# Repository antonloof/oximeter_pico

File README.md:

# Oximeter for the Raspberry pi PICO

ETA-dagen projekt 2022. Mäter din puls och visar den på ett par 7segmentsdisplayer

## 7 Segment
Använder [PIO](https://www.raspberrypi.com/news/what-is-pio/) för att [multiplexa](https://embedded-lab.com/blog/lab-11-multiplexing-seven-segment-led-displays/) displayerna.
PIO matas kontinuerligt av DMA med minimal interaktion från processorn. 

## Hur mäter man puls
Kort svar. Du mäter hur blodet rör sig i dina ådror. Syrerikt och syrfattigt blod absorberar och reflekterar olika mycket ljus.
Vi mäter hur mycket ljus som absorberar av bloded och får reda på om det finns mycket eller lite syre i blodet. 
Ett hjärtslag består av att först trycka ut syrerikt blod och sedan suga tillbaka syrefattigt blod. Det innenbär att ett slag innebär en ökning och sedan en miskning av mängden syre i blodet. Koden filtrerar först "hur mycket syre finns det i blodet"-signalen för att minska bruset. Efter det mäter den tiden mellan maximum av signalen. Detta är periodtiden på dina hjärtslag 1/period ger frekvens.

## Filter?
Vi använder ett 2a ordningens digitalt butterwurth filter. Ni kommer lära er mer om dessa snart (tm) i tex Kretsanalys. 

## Hur hittar vi maximum?
Vi letar efter toppar i signalen som omringas av en dal före och en dal efter. Dessa dalar måste vara "djupa" i förhållande till signalen för att vi ska räkna toppen som en topp. 

## Hur kommer man igång?
https://github.com/ndabas/pico-setup-windows
Ladda ner och kör, detta installerar vscode och toolchain för att bygga projektet och programmera din PICO.

## Vilken sektion?
E!

## Vilken färg?
GUL!

## Vilket skyddshelgon?
KALLE ANKA!

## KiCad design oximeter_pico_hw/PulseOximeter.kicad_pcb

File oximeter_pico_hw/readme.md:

# HW sidan av projektet

## Förklaring av schema

- U1 är våran mikrokontrollermodul, som sköter allting.
- U2 är själva sensor som mäter puls och blodsyrenivåer genom att lysa lite LEDs, som styrs med transistorer Q5-Q7, och mäta hur stark är ljuset efter den går igenom cellerna i din finger. Den innehåller en fotodiod, som släpper en viss mängd ström beroende på ljusstyrkan- tillsammans med R9 bildar den en sorts variabel spänningsdelare, och resulterande analogt värde läses av Pico:n.
- U3 och U4 är 7-segmentsdisplayer, och båda innehåller LED:s för 2 siffror. Segmenter tänds genom själva pinnarna av Pico:n, och transistorer Q1-Q4 väljer vilken segment ska lysa. Resistorer R1-R8 begränsar ström som segmenter ska ta.

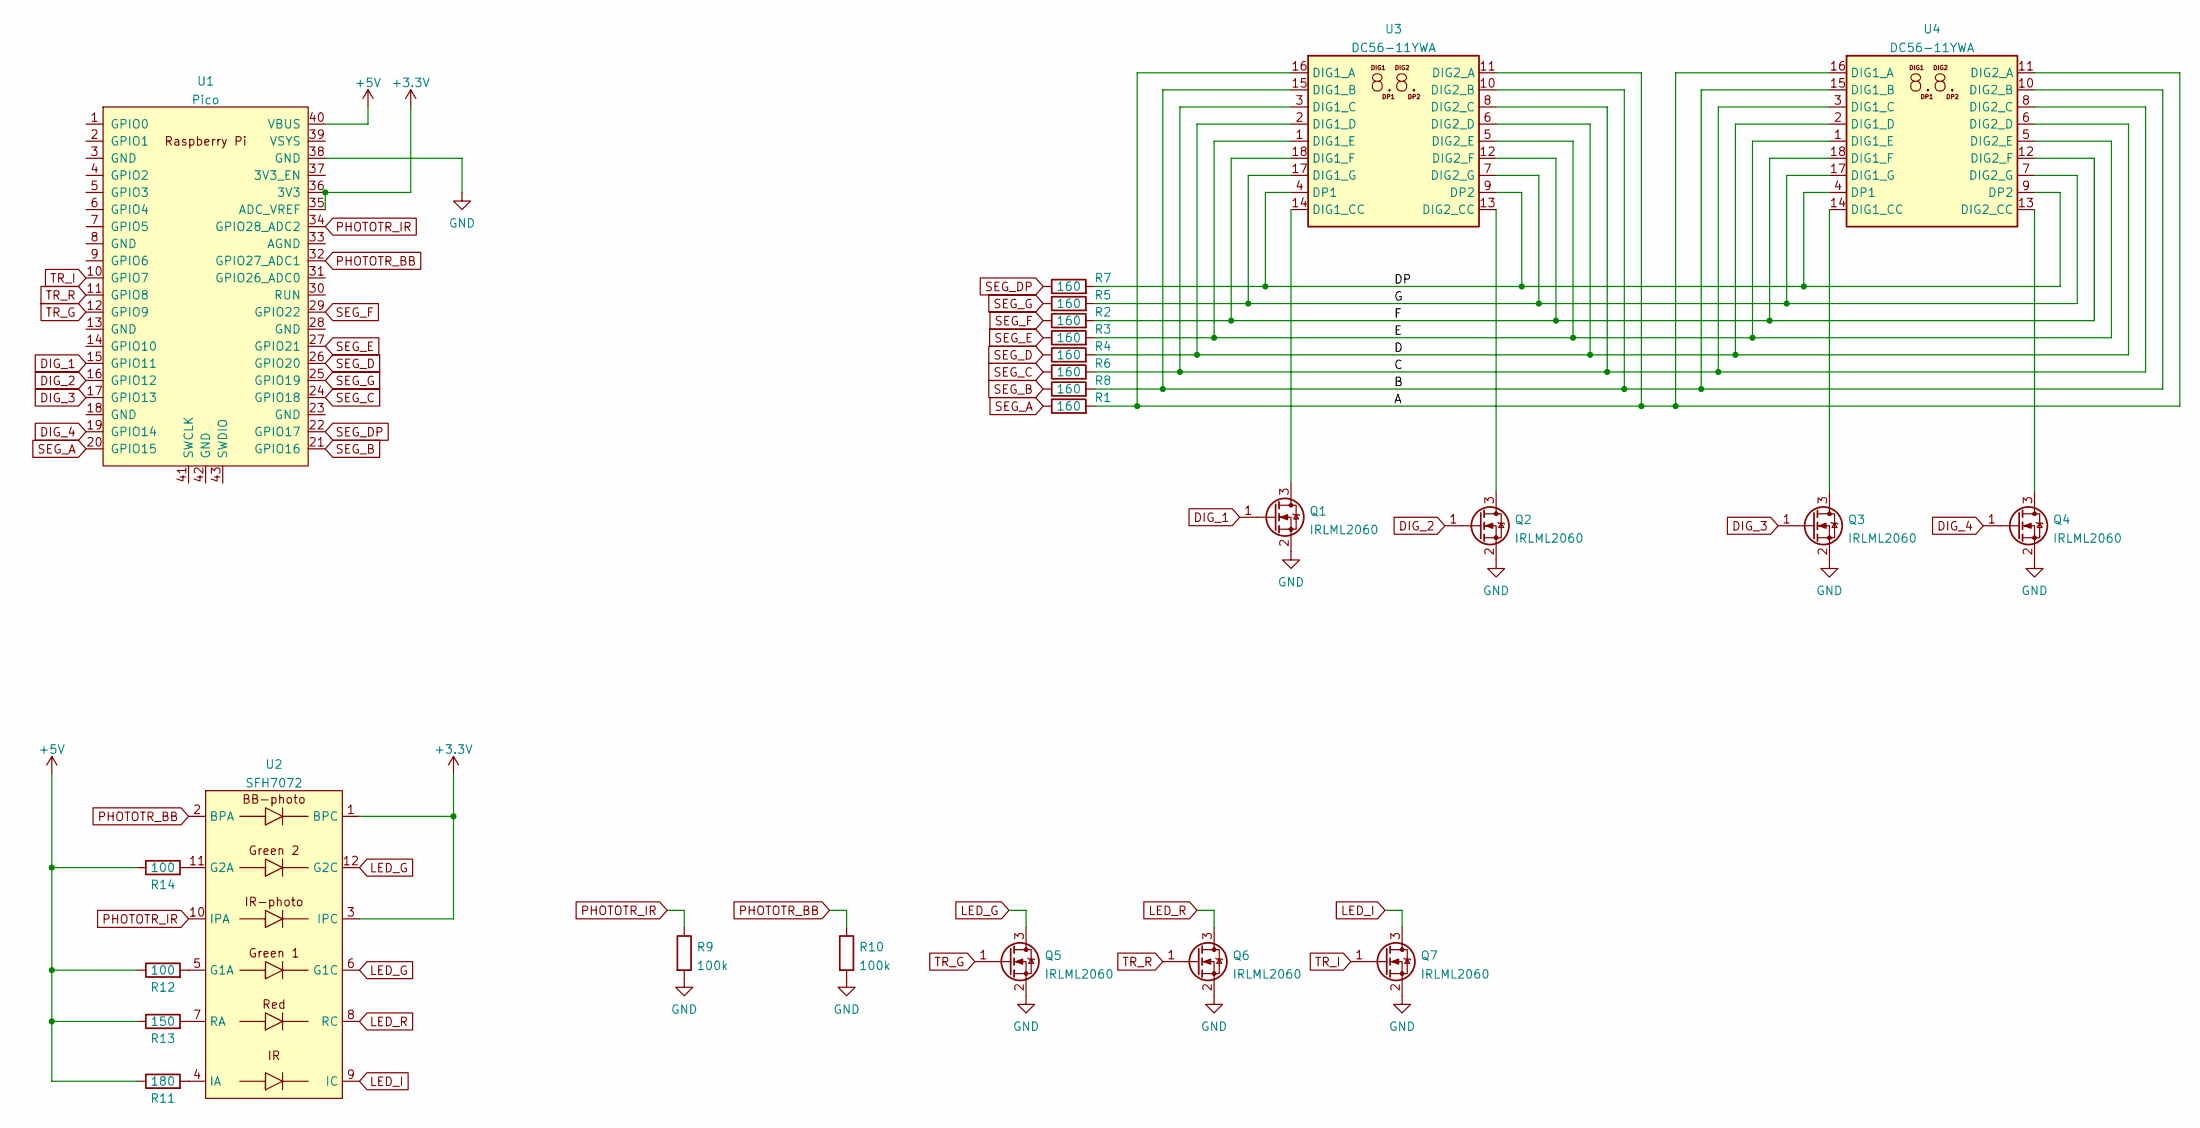
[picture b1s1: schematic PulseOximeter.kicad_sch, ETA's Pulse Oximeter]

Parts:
Q1, Q2, Q3, Q4, Q5, Q6, Q7: IRLML2060; SOT-23
R1, R2, R3, R4, R5, R6, R7, R8: 160; R_Axial_DIN0207_L6.3mm_D2.5mm_P15.24mm_Horizontal
R9, R10: 100k; R_Axial_DIN0207_L6.3mm_D2.5mm_P15.24mm_Horizontal
R11: 180; R_Axial_DIN0207_L6.3mm_D2.5mm_P15.24mm_Horizontal
R12, R14: 100; R_Axial_DIN0207_L6.3mm_D2.5mm_P15.24mm_Horizontal
R13: 150; R_Axial_DIN0207_L6.3mm_D2.5mm_P15.24mm_Horizontal
U1: Pico; RPi_Pico_SMD_TH
U2: SFH7072
U3, U4: DC56-11YWA; DA56-11SYKWA

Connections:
+3V3: U1.35 (ADC_VREF), U1.36 (3V3), U2.1 (BPC), U2.3 (IPC)
+5V: R11.1, R12.1, R13.1, R14.1, U1.40 (VBUS)
/A: R1.2, U3.11 (DIG2_A), U3.16 (DIG1_A), U4.11 (DIG2_A), U4.16 (DIG1_A)
/B: R8.2, U3.10 (DIG2_B), U3.15 (DIG1_B), U4.10 (DIG2_B), U4.15 (DIG1_B)
/C: R6.2, U3.3 (DIG1_C), U3.8 (DIG2_C), U4.3 (DIG1_C), U4.8 (DIG2_C)
/D: R4.2, U3.2 (DIG1_D), U3.6 (DIG2_D), U4.2 (DIG1_D), U4.6 (DIG2_D)
/DP: R7.2, U3.4 (DP1), U3.9 (DP2), U4.4 (DP1), U4.9 (DP2)
/E: R3.2, U3.1 (DIG1_E), U3.5 (DIG2_E), U4.1 (DIG1_E), U4.5 (DIG2_E)
/F: R2.2, U3.12 (DIG2_F), U3.18 (DIG1_F), U4.12 (DIG2_F), U4.18 (DIG1_F)
/G: R5.2, U3.7 (DIG2_G), U3.17 (DIG1_G), U4.7 (DIG2_G), U4.17 (DIG1_G)
DIG_1: Q1.1 (G), U1.15 (GPIO11)
DIG_2: Q2.1 (G), U1.16 (GPIO12)
DIG_3: Q3.1 (G), U1.17 (GPIO13)
DIG_4: Q4.1 (G), U1.19 (GPIO14)
GND: Q1.2 (S), Q2.2 (S), Q3.2 (S), Q4.2 (S), Q5.2 (S), Q6.2 (S), Q7.2 (S), R9.2, R10.2, U1.38 (GND)
LED_G: Q5.3 (D), U2.6 (G1C), U2.12 (G2C)
LED_I: Q7.3 (D), U2.9 (IC)
LED_R: Q6.3 (D), U2.8 (RC)
unnamed: Q1.3 (D), U3.14 (DIG1_CC)
unnamed: Q2.3 (D), U3.13 (DIG2_CC)
unnamed: Q3.3 (D), U4.14 (DIG1_CC)
unnamed: Q4.3 (D), U4.13 (DIG2_CC)
unnamed: R11.2, U2.4 (IA)
unnamed: R12.2, U2.5 (G1A)
unnamed: R13.2, U2.7 (RA)
unnamed: R14.2, U2.11 (G2A)
PHOTOTR_BB: R10.1, U1.32 (GPIO27_ADC1), U2.2 (BPA)
PHOTOTR_IR: R9.1, U1.34 (GPIO28_ADC2), U2.10 (IPA)
SEG_A: R1.1, U1.20 (GPIO15)
SEG_B: R8.1, U1.21 (GPIO16)
SEG_C: R6.1, U1.24 (GPIO18)
SEG_D: R4.1, U1.26 (GPIO20)
SEG_DP: R7.1, U1.22 (GPIO17)
SEG_E: R3.1, U1.27 (GPIO21)
SEG_F: R2.1, U1.29 (GPIO22)
SEG_G: R5.1, U1.25 (GPIO19)
TR_G: Q5.1 (G), U1.12 (GPIO9)
TR_I: Q7.1 (G), U1.10 (GPIO7)
TR_R: Q6.1 (G), U1.11 (GPIO8)

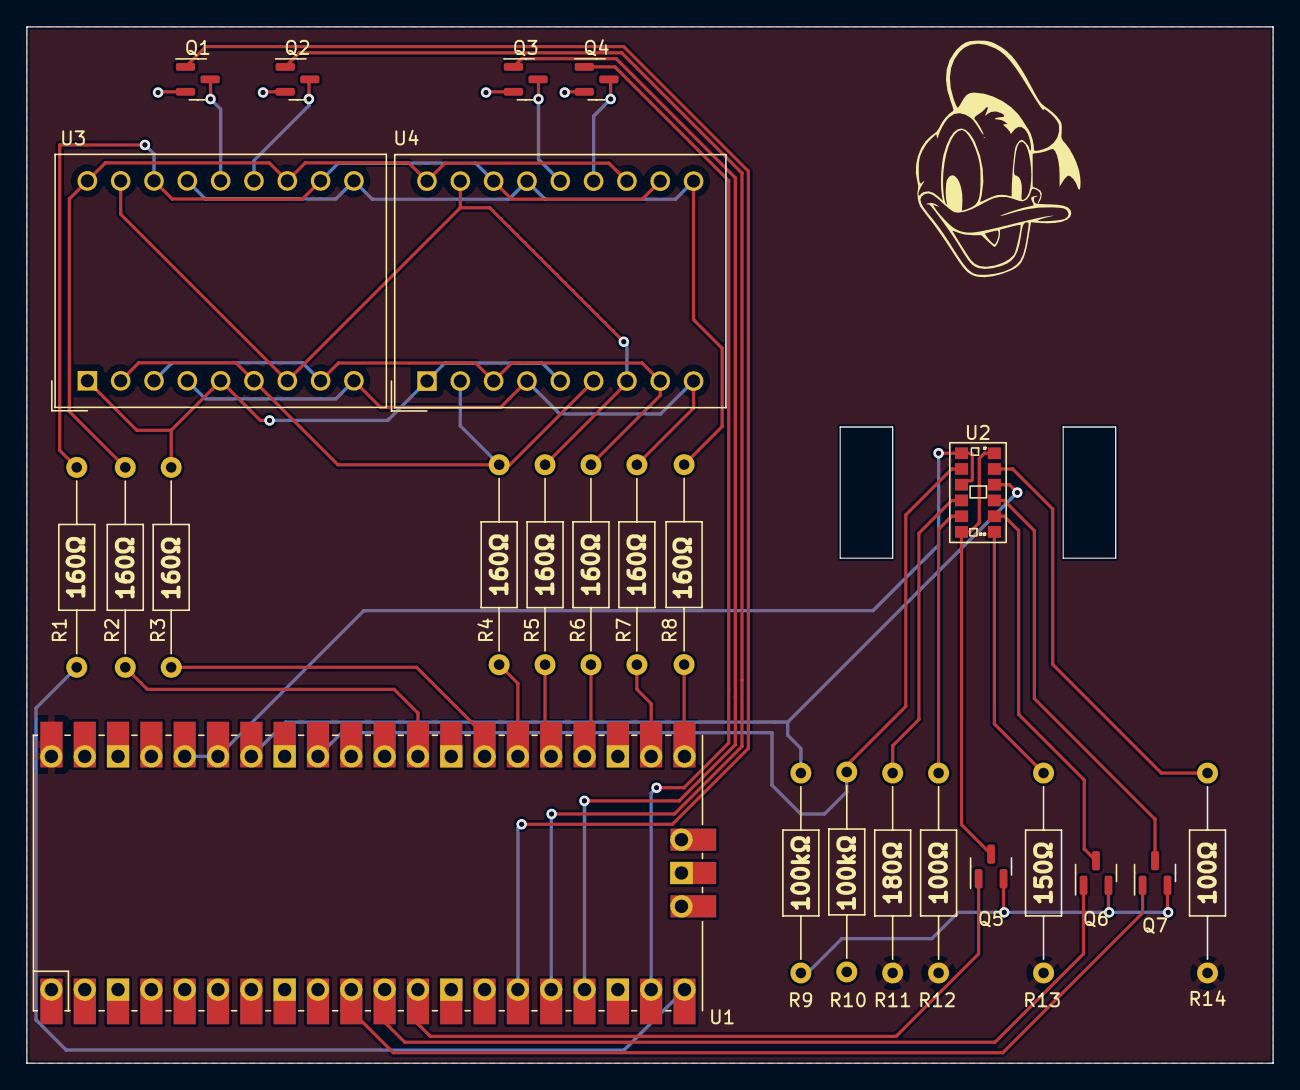
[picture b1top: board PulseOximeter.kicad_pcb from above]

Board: 2 copper layers, 95.0 x 79.0 mm, 25 parts (0 on the bottom side), 39 nets.

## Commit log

2022-07-13 add untested but built sw
2022-07-13 move test files
2022-07-13 skrev doc
2022-07-13 Add HW project files
2022-07-22 update 7seg driver
2022-07-22 tweak sw still not working
2022-08-24 Update HW to revision 2
2022-08-24 Update software to match the hardware
